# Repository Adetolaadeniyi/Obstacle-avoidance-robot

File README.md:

# Obstacle-avoidance-robot
This repository contains the circuit design, Arduino source code, and simulation files used to implement and test the obstacle avoidance robotic system.
The robot uses an ultrasonic sensor to measure the distance to nearby objects and adjusts its movement to avoid collisions in real time.

## Features
- Autonomous obstacle detection using an ultrasonic sensor
- Motor control using the L293D motor driver
- Real-time decision-making based on distance measurements
- Hardware design, simulation, and firmware implementation

## Hardware Components
- Arduino Uno
- Ultrasonic distance sensor (HC-SR04)
- L293D motor driver
- DC Gear motors
- NimH AA Battery

## Tools & Software
- Arduino IDE
- KiCad (schematic and PCB design)
- Proteus (circuit simulation)
- Tinkercad (virtual prototyping)

## How to Use
1. Upload the Arduino code to the microcontroller using the Arduino IDE.
2. View and test the circuit behavior using Proteus or Tinkercad simulations.
3. Open the KiCad files to inspect or modify the schematic and PCB layout.

## Contributors
- ADENIYI ADETOLA IDAYAT
- UNACHUKWU UCHE JONAS
- AWOSANYA AKOLADE OLUWATIMILEYIN
- OSEMWENGIE ESEOSA FAVOUR
- FABUSIWA BOLUWATIFE JEREMIAH 

## Notes
The Tinkercad simulation is provided as a shareable link due to Tinkercad’s cloud-based environment.

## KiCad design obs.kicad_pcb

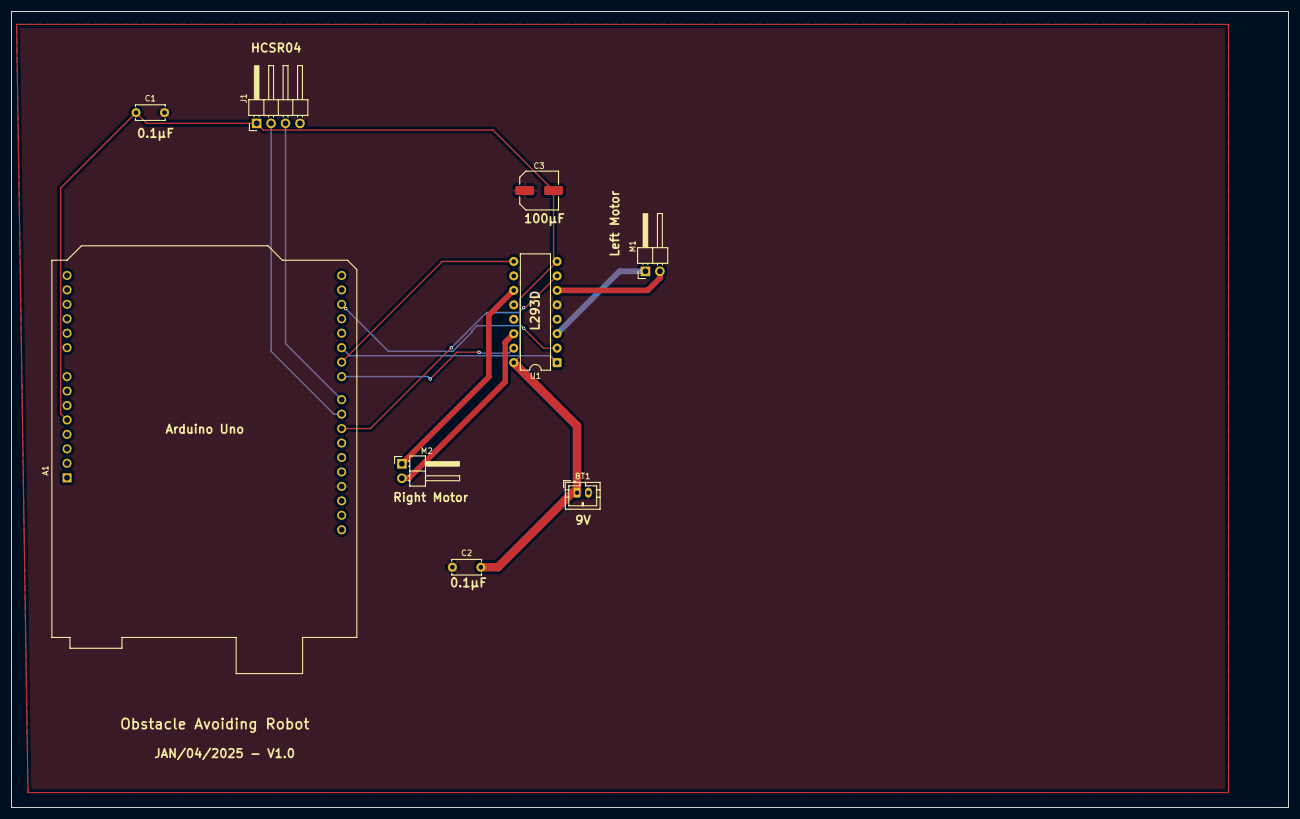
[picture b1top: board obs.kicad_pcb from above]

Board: 2 copper layers, 224.4 x 139.9 mm, 9 parts (0 on the bottom side), 13 nets.

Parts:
A1: Arduino_UNO_R3
BT1: 9V; JST_PH_B2B-PH-K_1x02_P2.00mm_Vertical
C1, C2: 0.1 μF; C_Disc_D5.0mm_W2.5mm_P5.00mm
C3: 100 μF; C_Elec_6.3x5.8
J1: HCSR04; PinHeader_1x04_P2.54mm_Horizontal
M1, M2: Motor_DC; PinHeader_1x02_P2.54mm_Horizontal
U1: L293D; DIP-16_W7.62mm

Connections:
/ECHO: A1.23 (D8), J1.3
/TRIG: A1.24 (D9), J1.2
GND: A1.29 (GND), BT1.2 (-), C1.2, C2.1, C3.1, J1.4, U1.5 (GND)
unnamed: A1.17 (D2), U1.2 (1A)
unnamed: A1.20 (D5), U1.1 (EN1,2)
unnamed: A1.21 (D6), U1.9 (EN3,4)
unnamed: A1.22 (D7), U1.15 (4A)
unnamed: A1.25 (D10), U1.7 (2A)
unnamed: M1.1 (+), U1.3 (1Y)
unnamed: M1.2 (-), U1.6 (2Y)
unnamed: M2.1 (+), U1.11 (3Y)
unnamed: M2.2 (-), U1.14 (4Y)
VCC: A1.5 (+5V), BT1.1 (+), C1.1, C2.2, C3.2, J1.1, U1.8 (VCC2), U1.16 (VCC1)

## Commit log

2026-01-29 Add Arduino code for obstacle detection and motor control
2026-01-29 Add Proteus simulation for obstacle avoidance robot
2026-01-29 Add KiCad schematic for obstacle avoidance robot
2026-01-29 Add PCB layout for robot controller board
2026-01-29 Add Gerber files for 2-layer PCB fabrication
2026-01-29 Create tinkercad_link.txt
    Add Tinkercad simulation link
2026-01-30 Add final project report for obstacle avoidance robot
2026-01-30 Add Tinkercad simulation link
